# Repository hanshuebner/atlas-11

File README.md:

# ATLAS-11 DCJ-11 I/O controller

ATLAS-11 is computer system based around the [DCJ11 microprocessor](https://dusted.dk/pages/computers/J-11/datasheet-DEC-DCJ11_Microprocessor_Users_Guide_OCR.pdf).  The DCJ11 is a VLSI implementation of the [PDP-11 minicomputer](https://en.wikipedia.org/wiki/PDP-11).  ATLAS-11 is based on the [DCJ-11 SBC CPU board](https://www.5volts.ch/pages/dcj11sbc/), designed by Peter Schranz, which hosts the CPU and the system RAM. An extension card with a [PGA2350 microcontroller board](https://shop.pimoroni.com/products/pga2350) implements the boot ROM, USB CDC serial ports and storage on an MicroSD card.  The system runs [FIG FORTH 1.3.3](http://www.stackosaurus.com/figforth.html).

## RP2350 GPIO / PIN usage

| GPIO Pin | Function | Description |
|----------|----------|-------------|
| GPIO 0   | UART0 TX | UART0 Transmit |
| GPIO 1   | UART0 RX | UART0 Receive |
| GPIO 2   | Power Control | Controls power to DCJ11 SBC |
| GPIO 5   | DAL0 | Data Address Line 0 |
| GPIO 6   | DAL1 | Data Address Line 1 |
| GPIO 7   | DAL2 | Data Address Line 2 |
| GPIO 8   | DAL3 | Data Address Line 3 |
| GPIO 9   | DAL4 | Data Address Line 4 |
| GPIO 10  | DAL5 | Data Address Line 5 |
| GPIO 11  | DAL6 | Data Address Line 6 |
| GPIO 12  | DAL7 | Data Address Line 7 |
| GPIO 13  | DAL8 | Data Address Line 8 |
| GPIO 14  | DAL9 | Data Address Line 9 |
| GPIO 15  | DAL10 | Data Address Line 10 |
| GPIO 16  | DAL11 | Data Address Line 11 |
| GPIO 17  | DAL12 | Data Address Line 12 |
| GPIO 18  | DAL13 | Data Address Line 13 |
| GPIO 19  | DAL14 | Data Address Line 14 |
| GPIO 20  | DAL15 | Data Address Line 15 |
| GPIO 21  | nBUFCTL | Buffer Control (Read/Write) |
| GPIO 22  | HALT | Halt signal |
| GPIO 23  | nALE | Address Latch Enable (negative logic) |
| GPIO 24  | nSCTL | Stretch Control |
| GPIO 25  | nCONT | Continue signal (negative logic) |
| GPIO 26  | INIT | Initialize signal |
| GPIO 27  | nIO | I/O access |
| GPIO 43 | SPI1_TX | SDCARD MOSI |
| GPIO 44 | SPI1_RX | SDCARD MISO |
| GPIO 45 | SPI1_CSn | SDCARD CS |
| GPIO 46 | SPI1_SCK | SDCARD SCK |

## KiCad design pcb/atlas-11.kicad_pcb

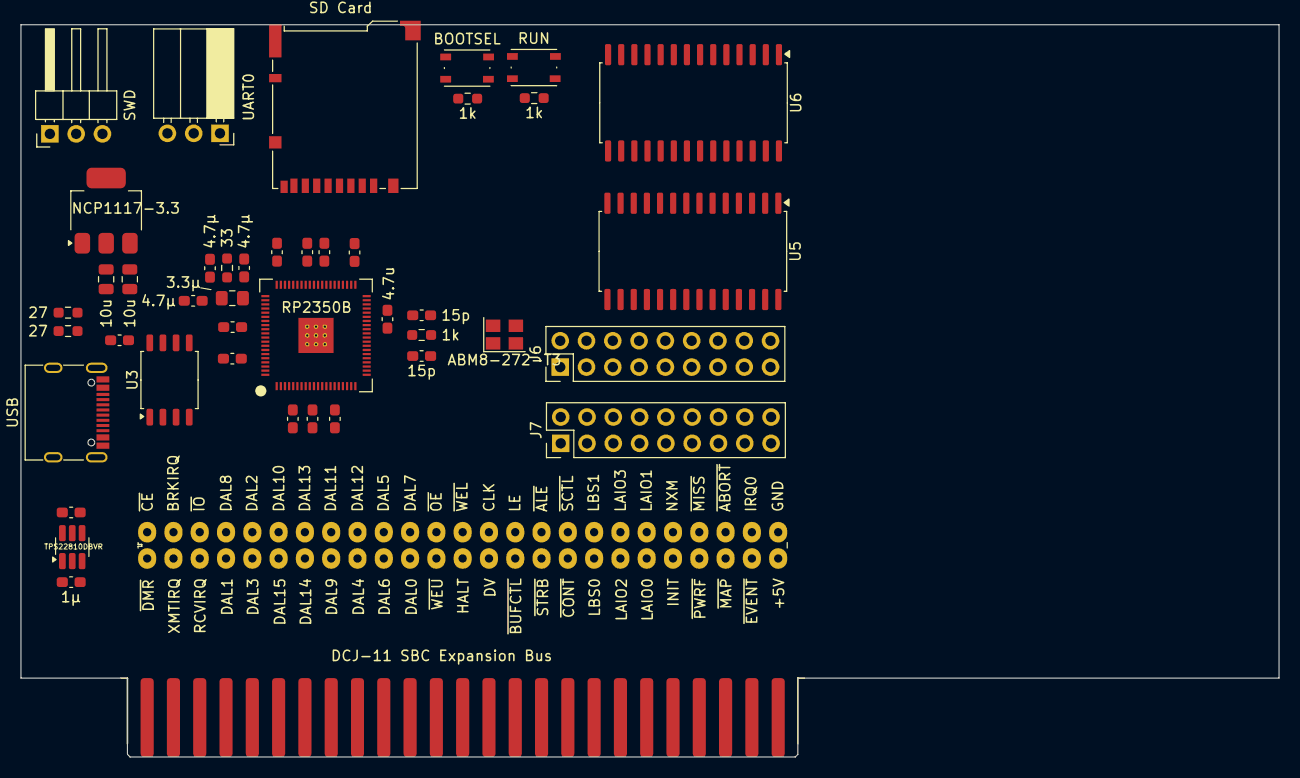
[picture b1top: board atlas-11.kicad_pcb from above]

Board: 2 copper layers, 121.5 x 70.7 mm, 44 parts (0 on the bottom side), 111 nets, no tracks yet.

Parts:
C1, C5: 10u; C_0805_2012Metric
C2, C8, C11, C12, C13, C14, C15, C16, C17, C18, C19: 100n; C_0603_1608Metric_Pad1.08x0.95mm_HandSolder
C3, C4: 15p; C_0603_1608Metric_Pad1.08x0.95mm_HandSolder
C7, C9, C21: 4.7µ; C_0603_1608Metric_Pad1.08x0.95mm_HandSolder
C10: 4.7u; C_0603_1608Metric_Pad1.08x0.95mm_HandSolder
C20: 1µ; C_0603_1608Metric_Pad1.08x0.95mm_HandSolder
J1: SD Card; microSD_HC_Hirose_DM3BT-DSF-PEJS
J2: DCJ-11 SBC Expansion Bus; Apple II Expansion Edge Connector
J3: SWD; PinHeader_1x03_P2.54mm_Horizontal
J4: DCJ-11 SBC Bus Probe Interface; DCJ-11 SBC Expansion Port Debug Header
J5: UART0; PinSocket_1x03_P2.54mm_Horizontal
J6: User Port; PinHeader_2x09_P2.54mm_Vertical
J7: Pico Bits; PinHeader_2x09_P2.54mm_Vertical
L1: 3.3µ; L_0805_2012Metric_Pad1.15x1.40mm_HandSolder
P1: USB; USB_C_Receptacle_G-Switch_GT-USB-7010ASV
R2, R4, R6: 1k; R_0603_1608Metric_Pad0.98x0.95mm_HandSolder
R5: 33; R_0603_1608Metric_Pad0.98x0.95mm_HandSolder
R7, R8: 27; R_0603_1608Metric_Pad0.98x0.95mm_HandSolder
SW1: BOOTSEL; SW_Push_1P1T_NO_Vertical_Wuerth_434133025816
SW2: RUN; SW_Push_1P1T_NO_Vertical_Wuerth_434133025816
U1: RP2350B; RP2350B_QFN-80_EP_10.573x10.573_Pitch0.4mm
U2: TPS22810DBVR; SOT-23-6_Handsoldering
U3: W25Q128JVS; SOIC-8_5.3x5.3mm_P1.27mm
U4: NCP1117-3.3; SOT-223-3_TabPin2
U5: MCP23017; SOIC-28W_7.5x17.9mm_P1.27mm
U6: MCP23017_SO; SOIC-28W_7.5x17.9mm_P1.27mm
Y1: ABM8-272-T3; Crystal_SMD_3225-4Pin_3.2x2.5mm

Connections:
+1V1: C7.1, C8.1, C10.1, C11.1, L1.1, U1.10 (DVDD), U1.32 (DVDD), U1.51 (DVDD), U1.65 (VREG_FB)
+3V3: C2.1, C5.1, C12.1, C13.1, C14.1, C15.1, C16.1, C17.1, C18.1, C21.1, J1.4 (VDD), J6.17, J7.17, R5.1, U1.5 (IOVDD), U1.15 (IOVDD), U1.24 (IOVDD), U1.29 (IOVDD), U1.41 (IOVDD), U1.50 (IOVDD), U1.59 (ADC_AVDD), U1.60 (IOVDD), U1.64 (VREG_VIN), U1.68 (USB_OTP_VDD), U1.69 (QSPI_IOVDD), U1.76 (IOVDD), U3.8 (VCC), U4.2 (VO), U5.9 (VDD), U6.9 (VDD), U6.15 (A0)
/BRKIRQ: J2.49, J4.49
/CLK: J2.37, J4.37
/DV: J2.14, J4.14
/IRQ0: J2.27, J4.27
/LAIO0: J2.20, J4.20
/LAIO1: J2.31, J4.31
/LAIO2: J2.19, J4.19
/LAIO3: J2.32, J4.32
/LBS0: J2.18, J4.18
/LBS1: J2.33, J4.33
/LE: J2.36, J4.36
/NXM: J2.30, J4.30
/QSPI_SCLK: U1.71 (QSPI_SCLK), U3.6 (CLK)
/QSPI_SD0: U1.72 (QSPI_SD0), U3.5 (DI/IO_{0})
/QSPI_SD1: U1.74 (QSPI_SD1), U3.2 (DO/IO_{1})
/QSPI_SD2: U1.73 (QSPI_SD2), U3.3 (~WP/IO_{2})
/QSPI_SD3: U1.70 (QSPI_SD3), U3.7 (~HOLD/~RESET/IO_{3})
/QSPI_SS: R6.1, U1.75 (QSPI_SS), U3.1 (~CS)
/RCVIRQ: J2.3, J4.3
/SWCLK: J3.3, U1.33 (SWCLK)
/SWDIO: J3.1, U1.34 (SWDIO)
/VREG_AVDD: C9.1, R5.2, U1.61 (VREG_AVDD)
/VREG_LX: L1.2, U1.63 (VREG_LX)
/XIN: C3.1, U1.30 (XIN), Y1.1
/XMTIRQ: J2.2, J4.2
/XOUT: R2.1, U1.31 (XOUT)
/~ABORT: J2.28, J4.28
/~CE: J2.50, J4.50
/~DMR: J2.1, J4.1
/~EVENT: J2.24, J4.24
/~MAP: J2.23, J4.23
/~MISS: J2.29, J4.29
/~OE: J2.39, J4.39
/~PWRF: J2.22, J4.22
/~STRB: J2.16, J4.16
/~WEL: J2.38, J4.38
/~WEU: J2.12, J4.12
DAL0: J2.11, J4.11, U1.2 (GPIO5)
DAL1: J2.4, J4.4, U1.3 (GPIO6)
DAL2: J2.46, J4.46, U1.4 (GPIO7)
DAL3: J2.5, J4.5, U1.6 (GPIO8)
DAL4: J2.9, J4.9, U1.7 (GPIO9)
DAL5: J2.41, J4.41, U1.8 (GPIO10)
DAL6: J2.10, J4.10, U1.9 (GPIO11)
DAL7: J2.40, J4.40, U1.11 (GPIO12)
DAL8: J2.47, J4.47, U1.12 (GPIO13)
DAL9: J2.8, J4.8, U1.13 (GPIO14)
DAL10: J2.45, J4.45, U1.14 (GPIO15)
DAL11: J2.43, J4.43, U1.16 (GPIO16)
DAL12: J2.42, J4.42, U1.17 (GPIO17)
DAL13: J2.44, J4.44, U1.18 (GPIO18)
DAL14: J2.7, J4.7, U1.19 (GPIO19)
DAL15: J2.6, J4.6, U1.20 (GPIO20)
GND: C1.2, C2.2, C3.2, C4.2, C5.2, C7.2, C8.2, C9.2, C10.2, C11.2, C12.2, C13.2, C14.2, C15.2, C16.2, C17.2, C18.2, C19.2, C20.2, C21.2, J1.6 (VSS), J2.26, J3.2, J4.26, J5.2, J6.18, J7.18, SW1.1, SW2.1, U1.62 (VREG_PGND), U1.81 (GND), U2.2 (GND), U3.4 (GND), U4.1 (GND), U5.10 (VSS), U5.15 (A0), U5.16 (A1), U5.17 (A2), U6.10 (VSS), U6.16 (A1), U6.17 (A2), Y1.2, Y1.4
GPIO28: J7.1, U1.36 (GPIO28)
GPIO29: J7.3, U1.37 (GPIO29)
GPIO30: J7.5, U1.38 (GPIO30)
GPIO31: J7.7, U1.39 (GPIO31)
GPIO32: J7.9, U1.40 (GPIO32)
GPIO33: J7.11, U1.42 (GPIO33)
GPIO34: J7.13, U1.43 (GPIO34)
GPIO35: J7.15, U1.44 (GPIO35)
HALT: J2.13, J4.13, U1.22 (GPIO22)
INIT: J2.21, J4.21, U1.27 (GPIO26)
unnamed: C4.1, R2.2, Y1.3
unnamed: J6.1, U5.1 (GPB0)
unnamed: J6.2, U5.21 (GPA0)
unnamed: J6.3, U5.2 (GPB1)
unnamed: J6.4, U5.22 (GPA1)
unnamed: J6.5, U5.3 (GPB2)
unnamed: J6.6, U5.23 (GPA2)
unnamed: J6.7, U5.4 (GPB3)
unnamed: J6.8, U5.24 (GPA3)
unnamed: J6.9, U5.5 (GPB4)
unnamed: J6.10, U5.25 (GPA4)
unnamed: J6.11, U5.6 (GPB5)
unnamed: J6.12, U5.26 (GPA5)
unnamed: J6.13, U5.7 (GPB6)
unnamed: J6.14, U5.27 (GPA6)
unnamed: J6.15, U5.8 (GPB7)
unnamed: J6.16, U5.28 (GPA7)
unnamed: P1.A1 (GND), P1.A12 (GND), P1.B1 (GND), P1.B12 (GND)
unnamed: P1.A4 (VBUS), P1.A9 (VBUS), P1.B4 (VBUS), P1.B9 (VBUS)
unnamed: R4.2, SW2.2
unnamed: R6.2, SW1.2
unnamed: R4.1, U1.35 (RUN)
unnamed: R8.2, U1.66 (USB_DM)
unnamed: R7.2, U1.67 (USB_DP)
SBC_ON: U1.79 (GPIO2), U2.3 (EN/UVLO)
SBC_POWER: C19.1, J2.25, J4.25, U2.6 (VOUT)
SCL: U1.52 (GPIO41_ADC1), U5.12 (SCK), U6.12 (SCK)
SDA: U1.49 (GPIO40_ADC0), U5.13 (SDA), U6.13 (SDA)
SDCARD_CLK: J1.5 (CLK), U1.57 (GPIO46_ADC6)
SDCARD_CS: J1.2 (DAT3/CD), U1.56 (GPIO45_ADC5)
SDCARD_DET: J1.9 (DET), U1.53 (GPIO42_ADC2)
SDCARD_MISO: J1.7 (DAT0), U1.55 (GPIO44_ADC4)
SDCARD_MOSI: J1.3 (CMD), U1.54 (GPIO43_ADC3)
SINTA: U1.45 (GPIO36), U6.20 (INTA)
SINTB: U1.46 (GPIO37), U6.19 (INTB)
UART0_RX: J5.1, U1.78 (GPIO1)
UART0_TX: J5.3, U1.77 (GPIO0)
UINTA: U1.47 (GPIO38), U5.20 (INTA)
UINTB: U1.48 (GPIO39), U5.19 (INTB)
VBUS: C1.1, C20.1, U2.1 (VIN), U4.3 (VI)
~ALE: J2.35, J4.35, U1.23 (GPIO23)
~BUFCTL: J2.15, J4.15, U1.21 (GPIO21)
~CONT: J2.17, J4.17, U1.26 (GPIO25)
~IO: J2.48, J4.48, U1.28 (GPIO27)
~SCTL: J2.34, J4.34, U1.25 (GPIO24)

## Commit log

2025-05-17 Firmware skeleton
2025-05-18 console mode
2025-05-18 convert to c++
2025-05-18 gpio symbols, halt command
2025-05-18 added bus monitor and sdcard, both wip
2025-05-19 getting somewhere
2025-05-20 bus interface testing wip
2025-05-21 fix display address
2025-05-21 device scaffolding
2025-05-21 dl11 implementation (untested)
2025-05-21 dl11 status registers
2025-05-21 start working on pio bus i/f
2025-05-21 pio bus interface compiles
2025-05-23 checkpoint pio bus interface
2025-05-23 moving sideways
2025-05-23 cont set, but still ignored
2025-05-23 can stretch cycle
2025-05-23 switch to unbuffered BS0/1
2025-05-25 Reorganize to add GAL code
2025-05-25 better /IO signal
2025-05-26 DCJ-11 SBC runs without hardware UART
2025-05-29 adapt to new hardware revision
2025-05-29 reorganize file system structure
2025-05-29 refactor cli for polled mode
2025-05-29 USB ports integrated
2025-05-29 five cdc ports
2025-05-29 multiport preparations (untested)
2025-05-30 configuration file reading
2025-05-30 LICENSE
2025-05-31 beginnings of the PCB design
2025-06-01 add more sections from rp2350 minimal example
2025-06-01 schematics & pcb work
2025-06-01 invert power on/off logic for tps22810 again
2025-06-01 fix tps22810 pinout
2025-06-02 pcb work
2025-06-03 trivialities
2025-06-07 update command interpreter (wip)
2025-06-07 static cdc<->dl11 association
2025-06-08 mixed up the queues
2025-06-08 Add ddboot5 boot load ROM
2025-06-09 checkpoint
2025-06-10 forth can read forth.bin from sdcard
2025-06-10 sd11 bootstrap
2025-06-22 checkpoint before adding second gal
